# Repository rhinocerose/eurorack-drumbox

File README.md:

# Drumbox

Check the website for up to date documentation

### [Bleepsound-Drumbox](https://bleepsound.github.io/drumbox/)

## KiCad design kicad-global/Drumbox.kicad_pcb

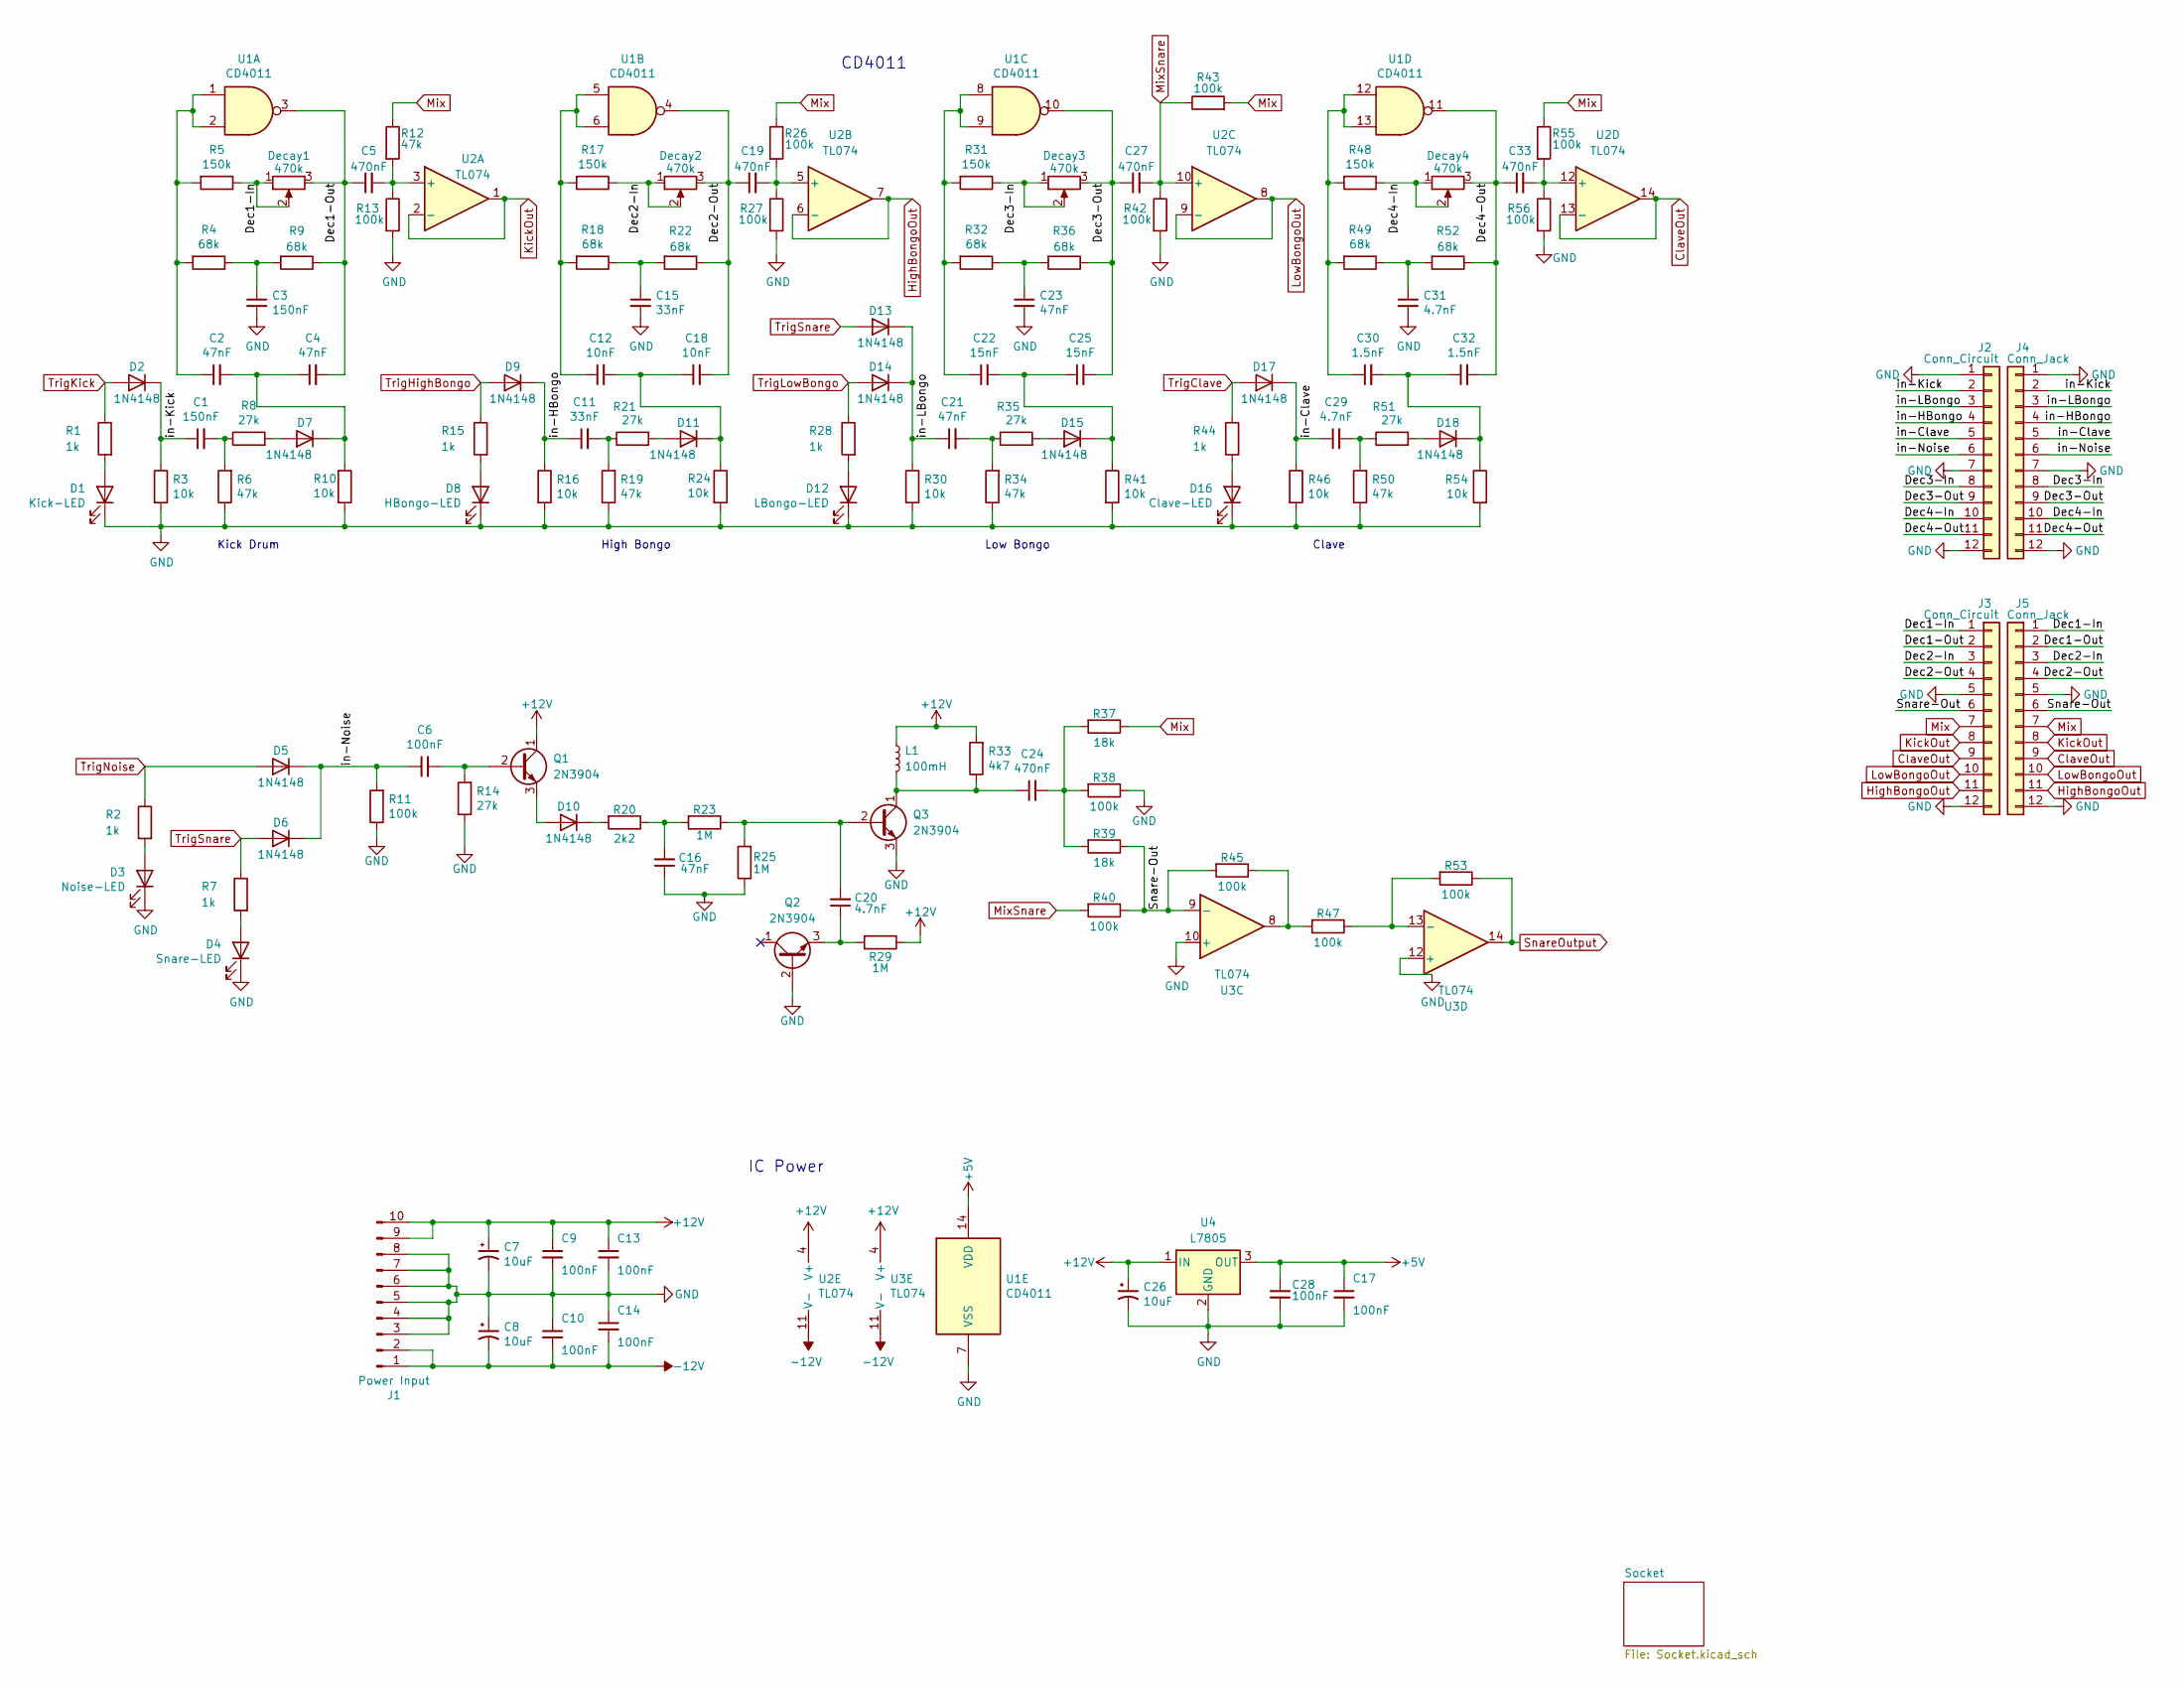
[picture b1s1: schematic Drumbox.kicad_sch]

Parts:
C1, C3: 150nF; C_Rect_L7.0mm_W3.5mm_P5.00mm
C2, C4, C16, C21, C23: 47nF; C_Rect_L7.0mm_W2.5mm_P5.00mm
C5, C19, C24, C27, C33: 470nF; C_Rect_L7.0mm_W3.5mm_P5.00mm
C6, C9, C10, C13, C14, C17, C28: 100nF; C_Disc_D7.0mm_W2.5mm_P5.00mm
C7, C8, C26: 10uF; CP_Radial_D5.0mm_P2.00mm
C11, C15: 33nF; C_Rect_L7.0mm_W2.5mm_P5.00mm
C12, C18: 10nF; C_Rect_L7.0mm_W2.5mm_P5.00mm
C20, C29: 4.7nF; C_Rect_L7.0mm_W2.5mm_P5.00mm
C22, C25: 15nF; C_Rect_L7.0mm_W3.5mm_P5.00mm
C30, C32: 1.5nF; C_Rect_L7.0mm_W2.5mm_P5.00mm
C31: 4.7nF; C_Rect_L7.0mm_W3.5mm_P5.00mm
D1: Kick-LED; LED_D4.0mm
D2, D5, D6, D7, D9, D10, D11, D13, D14, D15, D17, D18: 1N4148; D_DO-35_SOD27_P7.62mm_Horizontal
D3: Noise-LED; LED_D4.0mm
D4: Snare-LED; LED_D4.0mm
D8: HBongo-LED; LED_D4.0mm
D12: LBongo-LED; LED_D4.0mm
D16: Clave-LED; LED_D4.0mm
Decay1, Decay2, Decay3, Decay4: 470k; Pot-bourns-alpha
J1: Power Input; IDC-Header_2x05_P2.54mm_Vertical
J2, J3: Conn_Circuit; PinSocket_1x12_P2.54mm_Vertical
J4, J5: Conn_Jack; PinHeader_1x12_P2.54mm_Vertical
L1: 100mH; Inductor Coil
Q1, Q2, Q3: 2N3904; TO-92_Inline
R1, R2, R7, R15, R28, R44: 1k; R_Axial_DIN0207_L6.3mm_D2.5mm_P7.62mm_Horizontal
R3, R10, R16, R24, R30, R41, R46, R54: 10k; R_Axial_DIN0207_L6.3mm_D2.5mm_P7.62mm_Horizontal
R4, R9, R18, R22, R32, R36, R49, R52: 68k; R_Axial_DIN0207_L6.3mm_D2.5mm_P7.62mm_Horizontal
R5, R17, R31, R48: 150k; R_Axial_DIN0207_L6.3mm_D2.5mm_P7.62mm_Horizontal
R6, R12, R19, R34, R50: 47k; R_Axial_DIN0207_L6.3mm_D2.5mm_P7.62mm_Horizontal
R8, R14, R21, R35, R51: 27k; R_Axial_DIN0207_L6.3mm_D2.5mm_P7.62mm_Horizontal
R11, R13, R26, R27, R38, R40, R42, R43, R45, R47, R53, R55, R56: 100k; R_Axial_DIN0207_L6.3mm_D2.5mm_P7.62mm_Horizontal
R20: 2k2; R_Axial_DIN0207_L6.3mm_D2.5mm_P7.62mm_Horizontal
R23, R25, R29: 1M; R_Axial_DIN0207_L6.3mm_D2.5mm_P7.62mm_Horizontal
R33: 4k7; R_Axial_DIN0207_L6.3mm_D2.5mm_P7.62mm_Horizontal
R37, R39: 18k; R_Axial_DIN0207_L6.3mm_D2.5mm_P7.62mm_Horizontal
U1: CD4011; DIP-14_W7.62mm_Socket
U2, U3: TL074; DIP-14_W7.62mm_Socket
U4: L7805; TO-220-3_Vertical

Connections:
+5V: C17.1, C28.1, U1.14 (VDD), U4.3 (OUT)
+12V: C7.1, C9.1, C13.1, C26.1, J1.9, J1.10, L1.1, Q1.1 (C), R29.1, R33.2, U2.4 (V+), U3.4 (V+), U4.1 (IN); also elsewhere on the board
-12V: C8.2, C10.2, C14.2, J1.1, J1.2, U2.11 (V-), U3.11 (V-); also elsewhere on the board
/Dec1-In: Decay1.1, Decay1.2, J3.1, J5.1, R5.1
/Dec1-Out: C4.2, C5.1, Decay1.3, J3.2, J5.2, R9.1, U1.3
/Dec2-In: Decay2.1, Decay2.2, J3.3, J5.3, R17.1
/Dec2-Out: C18.2, C19.1, Decay2.3, J3.4, J5.4, R22.1, U1.4
/Dec3-In: Decay3.1, Decay3.2, J2.8, J4.8, R31.1
/Dec3-Out: C25.2, C27.1, Decay3.3, J2.9, J4.9, R36.1, U1.10
/Dec4-In: Decay4.1, Decay4.2, J2.10, J4.10, R48.1
/Dec4-Out: C32.2, C33.1, Decay4.3, J2.11, J4.11, R52.1, U1.11
/Snare-Out: J3.6, J5.6, R39.1, R40.1, R45.2, U3.9 (-)
/in-Clave: C29.1, D17.1 (K), J2.5, J4.5, R46.1
/in-HBongo: C11.1, D9.1 (K), J2.4, J4.4, R16.1
/in-Kick: C1.1, D2.1 (K), J2.2, J4.2, R3.1
/in-LBongo: C21.1, D13.1 (K), D14.1 (K), J2.3, J4.3, R30.1
/in-Noise: C6.1, D5.1 (K), D6.1 (K), J2.6, J4.6, R11.2
ClaveOut: J3.9, J5.9, U2.13 (-), U2.14; also elsewhere on the board
GND: C3.2, C7.2, C8.1, C9.2, C10.1, C13.2, C14.1, C15.2, C16.1, C17.2, C23.2, C26.2, C28.2, C31.2, D1.1 (K), D3.1 (K), D4.1 (K), D8.1 (K), D12.1 (K), D16.1 (K), J1.3, J1.4, J1.5, J1.6, J1.7, J1.8, J2.1, J2.7, J2.12, J3.5, J3.12, J4.1, J4.7, J4.12, J5.5, J5.12, Q2.2 (B), Q3.3 (E), R3.2, R6.1, R10.2, R11.1, R13.2, R14.1, R16.2, R19.1, R24.2, R25.1, R27.2, R30.2, R34.1, R38.1, R41.2, R42.2, R46.2, R50.1, R54.2, R56.2, U1.7 (VSS), U3.10 (+), U3.12 (+), U4.2 (GND); also elsewhere on the board
HighBongoOut: J3.11, J5.11, U2.6 (-), U2.7; also elsewhere on the board
KickOut: J3.8, J5.8, U2.1, U2.2 (-); also elsewhere on the board
LowBongoOut: J3.10, J5.10, U2.8, U2.9 (-); also elsewhere on the board
Mix: J3.7, J5.7, R12.1, R26.1, R37.1, R43.2, R55.1; also elsewhere on the board
MixSnare: C27.2, R40.2, R42.1, R43.1, U2.10 (+)
unnamed: C1.2, R6.2, R8.1
unnamed: C2.1, R4.2, R5.2, U1.1, U1.2
unnamed: C3.1, R4.1, R9.2
unnamed: C11.2, R19.2, R21.1
unnamed: C12.1, R17.2, R18.2, U1.5, U1.6
unnamed: C15.1, R18.1, R22.2
unnamed: C16.2, R20.1, R23.2
unnamed: C21.2, R34.2, R35.1
unnamed: C22.1, R31.2, R32.2, U1.8, U1.9
unnamed: C23.1, R32.1, R36.2
unnamed: C24.2, R37.2, R38.2, R39.2
unnamed: C29.2, R50.2, R51.1
unnamed: C30.1, R48.2, R49.2, U1.12, U1.13
unnamed: C31.1, R49.1, R52.2
unnamed: D1.2 (A), R1.2
unnamed: D3.2 (A), R2.2
unnamed: D4.2 (A), R7.2
unnamed: D7.2 (A), R8.2
unnamed: C2.2, C4.1, D7.1 (K), R10.1
unnamed: D8.2 (A), R15.2
unnamed: D10.2 (A), Q1.3 (E)
unnamed: D10.1 (K), R20.2
unnamed: D11.2 (A), R21.2
unnamed: C12.2, C18.1, D11.1 (K), R24.1
unnamed: D12.2 (A), R28.2
unnamed: D15.2 (A), R35.2
unnamed: C22.2, C25.1, D15.1 (K), R41.1
unnamed: D16.2 (A), R44.2
unnamed: D18.2 (A), R51.2
unnamed: C30.2, C32.1, D18.1 (K), R54.1
unnamed: C6.2, Q1.2 (B), R14.2
unnamed: C20.1, Q2.3 (E), R29.2
unnamed: C20.2, Q3.2 (B), R23.1, R25.2
unnamed: C24.1, L1.2, Q3.1 (C), R33.1
unnamed: R45.1, R47.2, U3.8
unnamed: C5.2, R12.2, R13.1, U2.3 (+)
unnamed: C19.2, R26.2, R27.1, U2.5 (+)
unnamed: C33.2, R55.2, R56.1, U2.12 (+)
unnamed: R47.1, R53.2, U3.13 (-)
SnareOutput: R53.1, U3.14; also elsewhere on the board
TrigClave: D17.2 (A), R44.1; also elsewhere on the board
TrigHighBongo: D9.2 (A), R15.1; also elsewhere on the board
TrigKick: D2.2 (A), R1.1; also elsewhere on the board
TrigLowBongo: D14.2 (A), R28.1; also elsewhere on the board
TrigNoise: D5.2 (A), R2.1; also elsewhere on the board
TrigSnare: D6.2 (A), D13.2 (A), R7.1; also elsewhere on the board

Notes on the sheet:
IC Power
High Bongo
Clave
Kick Drum
Low Bongo
CD4011

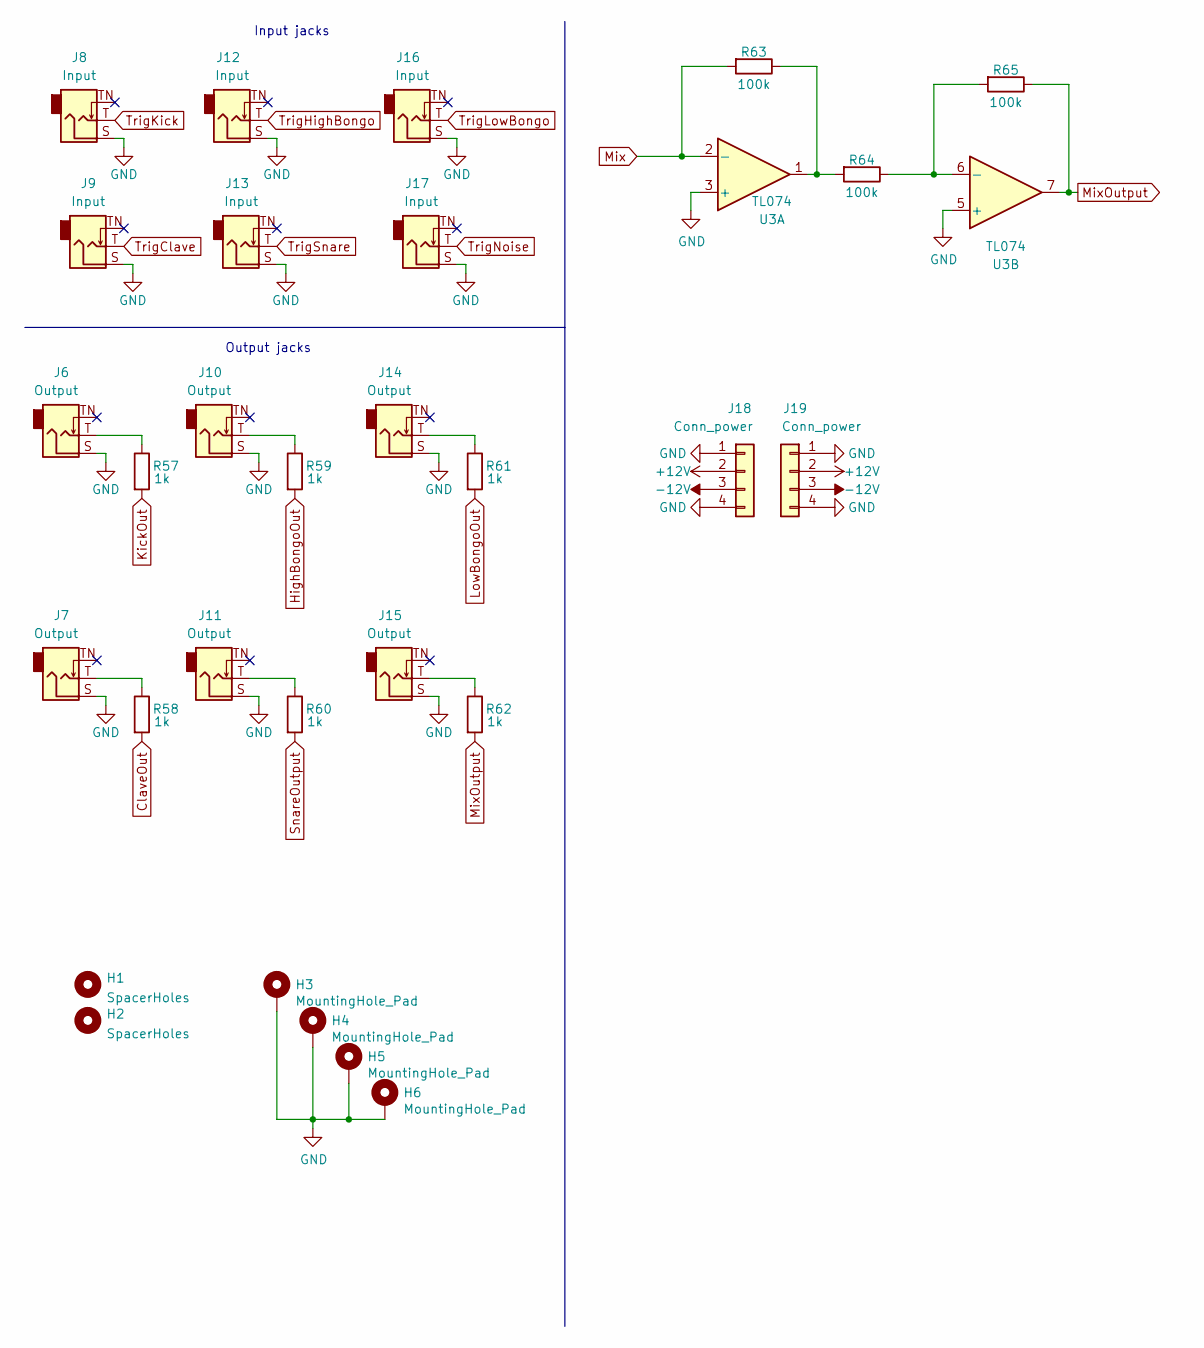
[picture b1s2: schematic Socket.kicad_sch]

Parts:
H1, H2: SpacerHoles; MountingHole_3.2mm_M3
H3, H4, H5, H6: MountingHole_Pad; Doepfer Mounting hole
J6, J7, J10, J11, J14, J15: Output; Thonkiconn
J8, J9, J12, J13, J16, J17: Input; Thonkiconn
J18: Conn_power; PinSocket_1x04_P2.54mm_Vertical
J19: Conn_power; PinHeader_1x04_P2.54mm_Vertical
R57, R58, R59, R60, R61, R62: 1k; R_Axial_DIN0207_L6.3mm_D2.5mm_P7.62mm_Horizontal
R63, R64, R65: 100k; R_Axial_DIN0207_L6.3mm_D2.5mm_P7.62mm_Horizontal
U3: TL074; DIP-14_W7.62mm_Socket

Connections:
+12V: J18.2, J19.2; also elsewhere on the board
-12V: J18.3, J19.3; also elsewhere on the board
ClaveOut: R58.2; also elsewhere on the board
GND: H3.1, H4.1, H5.1, H6.1, J6.S, J7.S, J8.S, J9.S, J10.S, J11.S, J12.S, J13.S, J14.S, J15.S, J16.S, J17.S, J18.1, J18.4, J19.1, J19.4, U3.3 (+), U3.5 (+); also elsewhere on the board
HighBongoOut: R59.2; also elsewhere on the board
KickOut: R57.2; also elsewhere on the board
LowBongoOut: R61.2; also elsewhere on the board
Mix: R63.2, U3.2 (-); also elsewhere on the board
MixOutput: R62.2, R65.1, U3.7
unnamed: J6.T, R57.1
unnamed: J7.T, R58.1
unnamed: J10.T, R59.1
unnamed: J11.T, R60.1
unnamed: J14.T, R61.1
unnamed: J15.T, R62.1
unnamed: R63.1, R64.2, U3.1
unnamed: R64.1, R65.2, U3.6 (-)
SnareOutput: R60.2; also elsewhere on the board
TrigClave: J9.T; also elsewhere on the board
TrigHighBongo: J12.T; also elsewhere on the board
TrigKick: J8.T; also elsewhere on the board
TrigLowBongo: J16.T; also elsewhere on the board
TrigNoise: J17.T; also elsewhere on the board
TrigSnare: J13.T; also elsewhere on the board

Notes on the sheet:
Input jacks
Output jacks

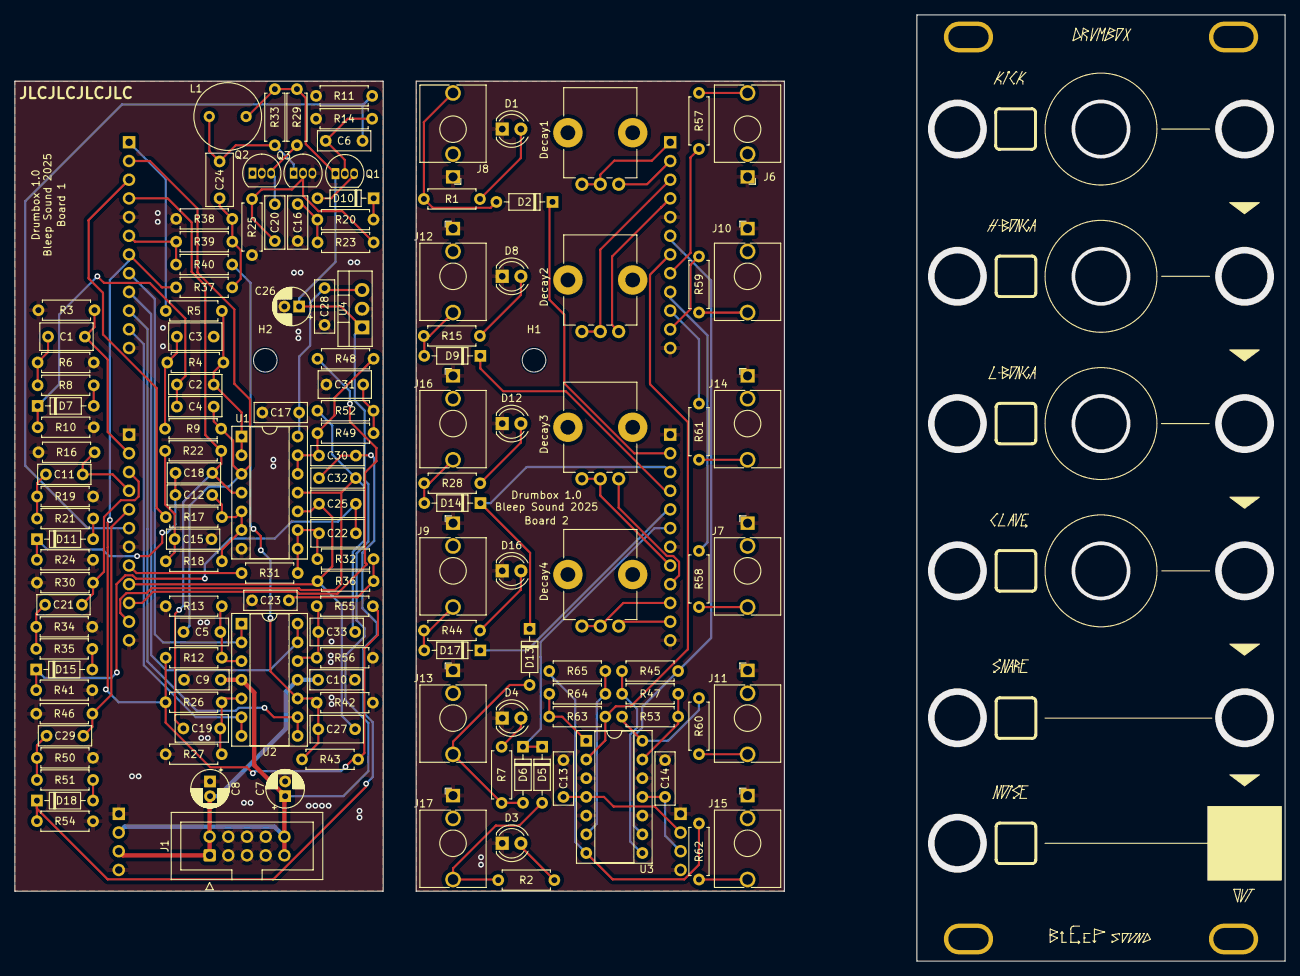
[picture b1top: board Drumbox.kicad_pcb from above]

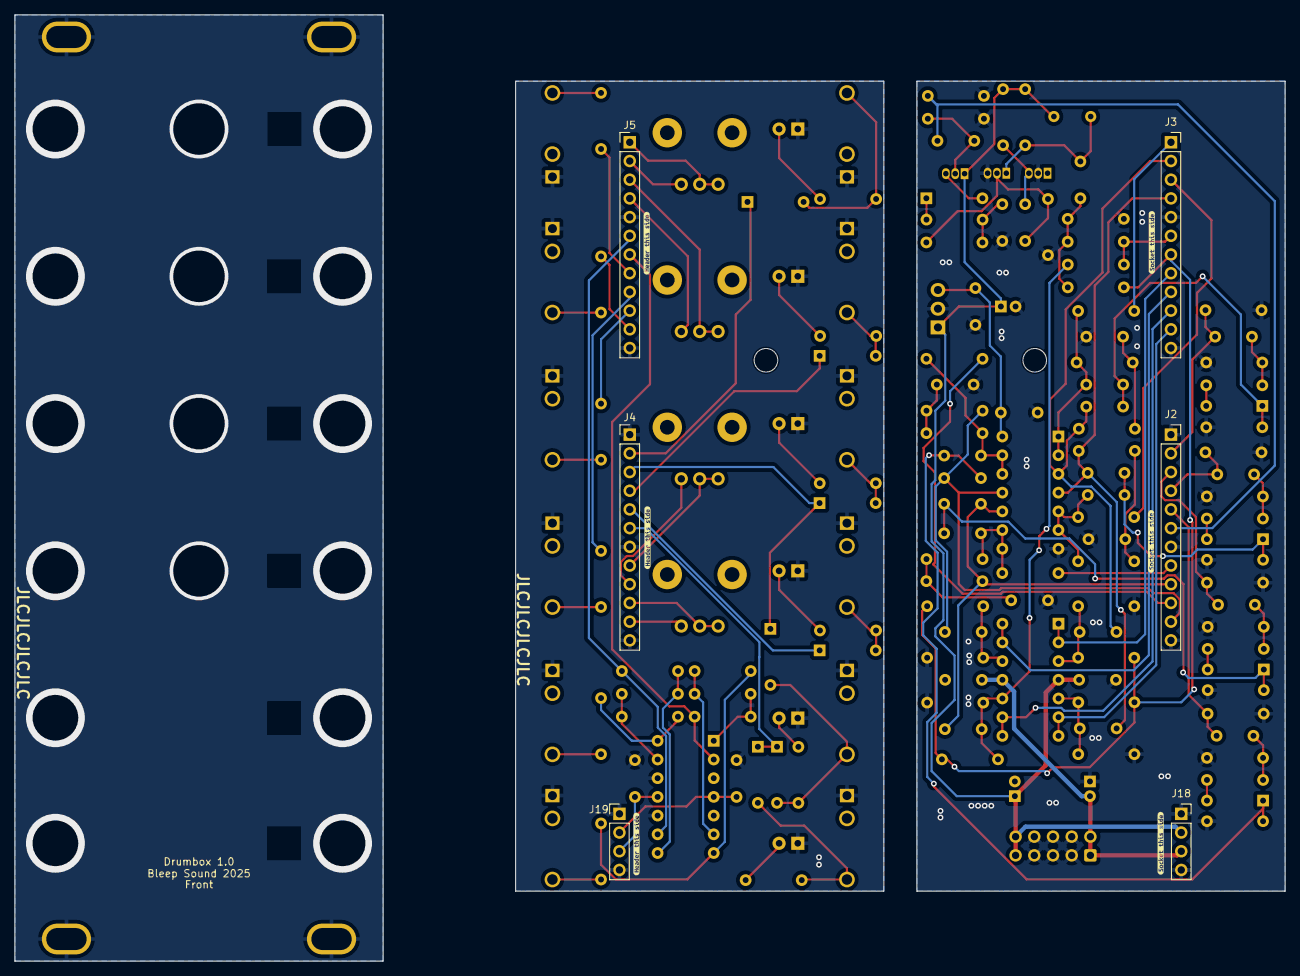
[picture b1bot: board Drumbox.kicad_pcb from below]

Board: 2 copper layers, 172.5 x 128.5 mm, 159 parts (12 on the bottom side), 79 nets.

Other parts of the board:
kibuzzard-67840646, kibuzzard-67840646#2, kibuzzard-67840646#3: G***; kibuzzard-67840646
kibuzzard-67840666, kibuzzard-67840666#2, kibuzzard-67840666#3: G***; kibuzzard-67840666

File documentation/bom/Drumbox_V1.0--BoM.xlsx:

Drumbox_V1.0 Bill of Materials
Schematic: | Drumbox | Component Groups: | 42
Variant: | default | Component Count: | 147 (0 SMD/ 144 THT)
Revision: | 1.0 | Fitted Components: | 147 (0 SMD/ 144 THT)
Date: | 2025-02-02 | Number of PCBs: | 1
KiCad Version: | 8.0.6-8.0.6-0~ubuntu22.04.1 | Total Components: | 147
Row | Description | References | Value | Quantity Per PCB | Links
1 | 100V 5% Polyester Film Box | C30 C32 | 1.5nF | 2 | https://www.taydaelectronics.com/capacitors/polyester-film-b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
2 | 100V 5% Polyester Film Box | C20 C29 | 4.7nF | 2 | https://www.taydaelectronics.com/capacitors/polyester-film-b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
3 | 100V 5% Polyester Film Box | C31 | 4.7nF | 1 | https://www.taydaelectronics.com/capacitors/polyester-film-b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
4 | 100V 5% Polyester Film Box | C12 C18 | 10nF | 2 | https://www.taydaelectronics.com/capacitors/polyester-film-b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
5 | 100V 5% Polyester Film Box | C22 C25 | 15nF | 2 | https://www.taydaelectronics.com/capacitors/polyester-film-b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
6 | 100V 5% Polyester Film Box | C11 C15 | 33nF | 2 | https://www.taydaelectronics.com/capacitors/polyester-film-b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
7 | 100V 5% Polyester Film Box | C2 C4 C16 C21 C23 | 47nF | 5 | https://www.taydaelectronics.com/capacitors/polyester-film-b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
8 | Ceramic disc capacitor 50V 20% | C6 C9 C10 C13 C14 C17 C28 | 100nF | 7 | https://www.taydaelectronics.com/capacitors/ceramic-disc-cap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
9 | 100V 5% Polyester Film Box | C1 C3 | 150nF | 2 | https://www.taydaelectronics.com/capacitors/polyester-film-b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
10 | 100V 5% Polyester Film Box | C5 C19 C24 C27 C33 | 470nF | 5 | https://www.taydaelectronics.com/capacitors/polyester-film-b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
11 | 10uF Electrolytic capacitor, 2.0mm pitch, 5mm diameter | C7 C8 C26 | 10uF | 3 | https://www.taydaelectronics.com/capacitors/electrolytic-cap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
12 | 1N4148 Switching diode | D2 D5 D6 D7 D9 D10 D11 D13 D14 D15 D17 D18 | 1N4148 | 12 | https://www.taydaelectronics.com/1n4148-switching-signal-diode.html
13 | 4 or 5mm THT LED | D16 | Clave-LED | 1 | https://www.taydaelectronics.com/leds/round-leds/5mm-leds.html
14 | 4 or 5mm THT LED | D8 | HBongo-LED | 1 | https://www.taydaelectronics.com/leds/round-leds/5mm-leds.html
15 | 4 or 5mm THT LED | D1 | Kick-LED | 1 | https://www.taydaelectronics.com/leds/round-leds/5mm-leds.html
16 | 4 or 5mm THT LED | D12 | LBongo-LED | 1 | https://www.taydaelectronics.com/leds/round-leds/5mm-leds.html
17 | 4 or 5mm THT LED | D3 | Noise-LED | 1 | https://www.taydaelectronics.com/leds/round-leds/5mm-leds.html
18 | 4 or 5mm THT LED | D4 | Snare-LED | 1 | https://www.taydaelectronics.com/leds/round-leds/5mm-leds.html
19 | Alpha/bourns vertical potentiometer | Decay1 Decay2 Decay3 Decay4 | 470k | 4 | https://www.thonk.co.uk/shop/alpha-9mm-pots/
20 | 2.54mm pitch pin socket vertical 1x12pos | J2 J3 | Conn_Circuit | 2
21 | 2.54mm pitch pin header vertical 1x12pos | J4 J5 | Conn_Jack | 2
22 | 2.54mm pitch pin socket vertical 1x4pos | J18 | Conn_power | 1
23 | 2.54mm pitch pin header vertical 1x4pos | J19 | Conn_power | 1
24 | Thonkiconn jack | J8 J9 J12 J13 J16 J17 | Input | 6 | https://www.thonk.co.uk/shop/thonkiconn/
25 | Thonkiconn jack | J6 J7 J10 J11 J14 J15 | Output | 6 | https://www.thonk.co.uk/shop/thonkiconn/
26 | Eurorack 10 pin shrouded power header IDC | J1 | Power Input | 1 | https://www.thonk.co.uk/shop/eurorack-diy-essentials/
27 | Inductor 100mH 5mm Pitch 9x13 (DxH) | L1 | 100mH | 1 | https://www.ebay.co.uk/itm/293453947951?var=592268786436
28 | 2N3904 NPN General Purpose Transistor | Q1 Q2 Q3 | 2N3904 | 3 | https://www.taydaelectronics.com/2n3904-npn-general-propose-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
29 | 2.5mm*6.8mm 1/4W 1% Metal film resistor | R1 R2 R7 R15 R28 R44 R57 R58 R59 R60 R61 R62 | 1k | 12 | https://www.taydaelectronics.com/resistors/1-4w-metal-film-r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
30 | 2.5mm*6.8mm 1/4W 1% Metal film resistor | R20 | 2k2 | 1 | https://www.taydaelectronics.com/resistors/1-4w-metal-film-r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
31 | 2.5mm*6.8mm 1/4W 1% Metal film resistor | R33 | 4k7 | 1 | https://www.taydaelectronics.com/resistors/1-4w-metal-film-r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
32 | 2.5mm*6.8mm 1/4W 1% Metal film resistor | R3 R10 R16 R24 R30 R41 R46 R54 | 10k | 8 | https://www.taydaelectronics.com/resistors/1-4w-metal-film-r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
33 | 2.5mm*6.8mm 1/4W 1% Metal film resistor | R37 R39 | 18k | 2 | https://www.taydaelectronics.com/resistors/1-4w-metal-film-r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
34 | 2.5mm*6.8mm 1/4W 1% Metal film resistor | R8 R14 R21 R35 R51 | 27k | 5 | https://www.taydaelectronics.com/resistors/1-4w-metal-film-r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
35 | 2.5mm*6.8mm 1/4W 1% Metal film resistor | R6 R12 R19 R34 R50 | 47k | 5 | https://www.taydaelectronics.com/resistors/1-4w-metal-film-r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
36 | 2.5mm*6.8mm 1/4W 1% Metal film resistor | R4 R9 R18 R22 R32 R36 R49 R52 | 68k | 8 | https://www.taydaelectronics.com/resistors/1-4w-metal-film-r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
37 | 2.5mm*6.8mm 1/4W 1% Metal film resistor | R11 R13 R26 R27 R38 R40 R42 R43 R45 R47 R53 R55 R56 R63 R64 R65 | 100k | 16 | https://www.taydaelectronics.com/resistors/1-4w-metal-film-r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
38 | 2.5mm*6.8mm 1/4W 1% Metal film resistor | R5 R17 R31 R48 | 150k | 4 | https://www.taydaelectronics.com/resistors/1-4w-metal-film-r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
39 | 2.5mm*6.8mm 1/4W 1% Metal film resistor | R23 R25 R29 | 1M | 3 | https://www.taydaelectronics.com/resistors/1-4w-metal-film-r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
40 | CD4011B or CD4011A, Quad NAND Gate | U1 | CD4011 | 1
41 | Positive 1.5A 35V Linear Regulator, Fixed Output 5V, TO-220/TO-263/TO-252 | U4 | L7805 | 1
42 | Quad Low-Noise JFET-Input Operational Amplifiers, DIP-14/SOIC-14 | U2 U3 | TL074 | 2 | https://www.thonk.co.uk/shop/eurorack-diy-essentials/

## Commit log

2025-02-02 v1.0
2025-02-02 fix issue with front
2025-08-12 Update submodules to track main branch
2025-08-12 Update submodules: set branch=main and fix URLs
2025-08-12 Update submodules: add branch=main and fix URLs
2025-08-13 Remove .gitmodules (no submodules exist)
